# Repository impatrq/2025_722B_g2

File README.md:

# AQUILES - Exoesqueleto de Asistencia Motora

<div align="center">
  
  <h3>Revolucionando la movilidad humana</h3>
  <p>Exoesqueleto de asistencia motora con inteligencia artificial</p>
  
  <!-- Íconos de redes sociales -->
<p align="center">
  &nbsp;&nbsp;&nbsp;&nbsp;
  &nbsp;&nbsp;&nbsp;&nbsp;
  &nbsp;&nbsp;&nbsp;&nbsp;
  
</p>
</div>

## 🌐 Accede a la Página Web

🔗 [Visita Aquiles Web](https://aquilesproject.com/)

## ✨ Revolucionando la Movilidad Humana

AQUILES es un exoesqueleto de asistencia motora diseñado para mejorar la movilidad de personas con debilidad muscular, fatiga crónica o dificultades motrices. Este sistema innovador reduce el esfuerzo físico del usuario, permitiendo una marcha más eficiente y menos agotadora.

## 🔧 Características Principales

- **Asistencia Inteligente**: AQUILES integra inteligencia artificial para adaptar su funcionamiento a las necesidades del usuario en tiempo real.
- **Sistema de Ajuste**: Un botón permite regular el nivel de asistencia, facilitando la rehabilitación progresiva y el fortalecimiento muscular.
- **Diseño Ergonómico y Ligero**: Fabricado con materiales resistentes y de bajo peso para garantizar comodidad y facilidad de uso.
- **Sensores Avanzados**: Incluye acelerómetros y encoders para monitorear el movimiento y optimizar la asistencia.
- **Monitor de Salud**: Registra calorías quemadas y mide el pulso mediante un sensor ubicado en la arteria femoral.
- **Aplicaciones en Rehabilitación**: Ideal para programas médicos donde los especialistas pueden ajustar la asistencia según la evolución del paciente.
- **Baterías Intercambiables**: Ofrece una autonomía de 45 minutos con baterías compactas y fáciles de reemplazar.

## 👨‍👩‍👦🛠️ Aplicaciones

- **Personas con movilidad reducida**: AQUILES reduce el esfuerzo necesario para caminar.
- **Personas con sobrepeso o alta estatura**: Ayuda a disminuir la carga en articulaciones y músculos.
- **Adultos mayores**: Facilita la marcha y reduce la fatiga muscular.
- **Rehabilitación física**: Ajuste progresivo para recuperar fuerza y movilidad.
- **Deporte y fitness**: Apoya la resistencia y optimiza el rendimiento físico.

## ⚡ Tecnología Utilizada

- **Hardware**:

  - Raspberry Pi 4
  - Sensores de aceleración y encoders
  - Motores brushless con controladores ESC
  - Baterías LiPo 3S 5000mAh 70C
  - Pulsadores y sistema de ajuste de asistencia

- **Software**:
  - Programación en C/C++ y Python
  - Algoritmos de Machine Learning para optimización de asistencia
  - Integración con microcontroladores RP2040
  - Flutter para la aplicación móvil
  - Firebase para la base de datos

## 💸 Costos Estimados

El desarrollo de AQUILES tiene un costo estimado de **378 USD**, incluyendo componentes electrónicos, motores y materiales de fabricación.

## 📢 Contribución

Si deseas colaborar con el desarrollo de AQUILES, puedes contribuir con:

- Mejoras en el código
- Optimización de hardware
- Documentación y pruebas
- Aportes económicos para investigación y desarrollo

## 🛠️ Instalación y Uso

1. Clona el repositorio:
   ```bash
   git clone https://github.com/tu-usuario/aquiles.git
   ```
2. Instala las dependencias necesarias.
3. Carga el firmware en la Raspberry Pi 4.
4. Conecta los motores y sensores.
5. Ajusta el nivel de asistencia y comienza a probar AQUILES.

## 📈 Futuro del Proyecto

- Implementación de algoritmos de IA más avanzados.
- Desarrollo de una aplicación móvil para el monitoreo en tiempo real.
- Optimización del consumo energético para aumentar la autonomía.
- Pruebas con usuarios reales para mejorar la experiencia de uso.

## Integrantes:

### Juan Montilla

- 📷 Instagram: [@montillajuanignacio](https://www.instagram.com/montillajuanignacio/)
- 📧 Mail: montillajuanignacio@gmail.com
- 🏆 LinkedIn:[Juan Montilla](https://www.linkedin.com/in/juan-ignacio-montilla-b98064358/)
- 🌐 Github: [@monti3](github.com/monti3)

### Santiago Alberto Zacarías

- 📷 Instagram: [@santizaca\_](https://www.instagram.com/santizaca_/)
- 📧 Mail: sanfran120771@gmail.com
- 🏆 LinkedIn: [Santiago Zacarias](https://www.linkedin.com/in/santiago-zacar%C3%ADas-3a3978319/)
- 🌐 Github: [ZaCoso](https://github.com/ZaCoso)

### Juan Cruz Isola

- 📷 Instagram: [@juanisola\_](https://www.instagram.com/juanisola_/)
- 📧 Mail: juancruz.isola2209@gmail.com
- 🏆 LinkedIn: [Juan Cruz Isola](https://www.linkedin.com/in/juan-cruz-isola-11309035a/)
- 🌐 Github: [juanisola\_](https://github.com/juanisola)

### Rodrigo Alexis Lin

- 📷 Instagram: [@alexisrodrigolin](https://www.instagram.com/alexisrodrigolin/)
- 📧 Mail: alexisrodrigolin@gmail.com
- 🏆 LinkedIn: [Rodrigo Alexis Lin](https://www.linkedin.com/in/rodrigo-lin-61210a35b/)
- 🌐 Github: [alexisrodrigolin](https://github.com/alexisrodrigolin)

### Mauricio Contardi Trillo

- 📷 Instagram: [@mauritrillo\_](https://www.instagram.com/mauritrillo_/)
- 📧 Mail: trillocontardimauricio@gmail.com
- 🏆 LinkedIn: [Mauricio Contardi Trillo](https://www.linkedin.com/in/mauricio-trillo-contardi-68bbba35a/)
- 🌐 Github: [Mauriciotrillo](https://github.com/MauricioTrillo)

### Misael Castillo

- 📷 Instagram: [@misaacas](https://www.instagram.com/misaacas/)
- 📧 Mail: misacastillo08@gmail.com
- 🏆 LinkedIn: [Castillo Misael](https://www.linkedin.com/in/misael-castillo-0a52a1314/)
- 🌐 Github: [misaacastillo](https://github.com/misaacastillo)

---

AQUILES es más que un proyecto tecnológico: es una solución que redefine la movilidad humana. ¡Sé parte de la revolución! 💪🛠️

## 📜 Licencia

Este proyecto está licenciado bajo la [MIT License](LICENSE).  
© 2025 Aquiles.corp.

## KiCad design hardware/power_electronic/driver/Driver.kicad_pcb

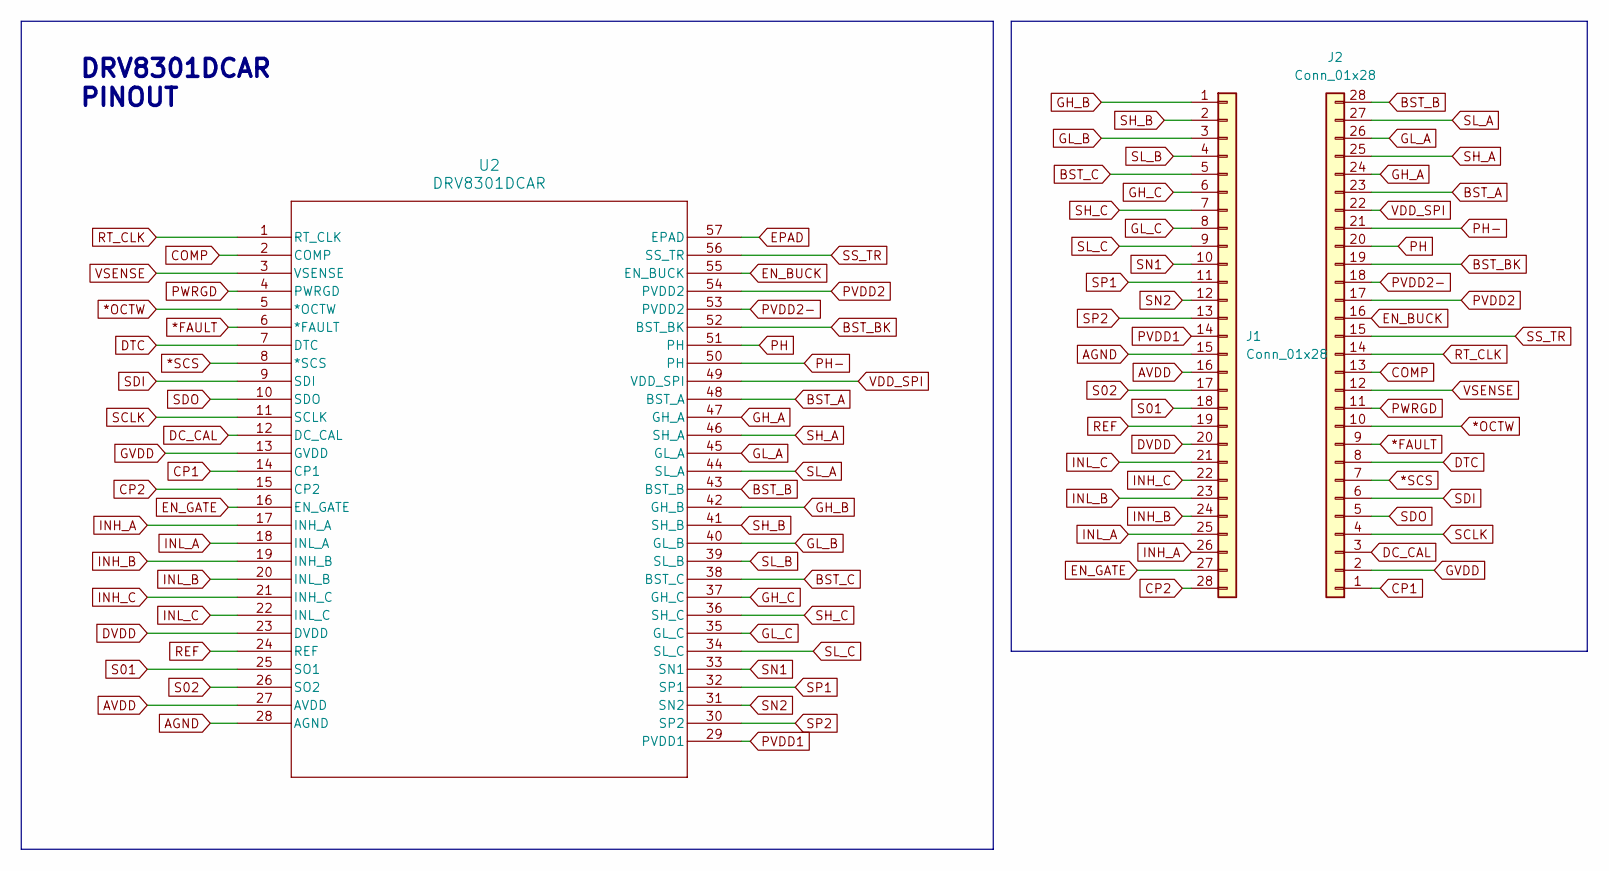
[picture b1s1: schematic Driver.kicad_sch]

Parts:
J1, J2: Conn_01x28; PinHeader_1x28_P2.54mm_Vertical
U2: DRV8301DCAR; DRV8301DCAR PADGND

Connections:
*FAULT: J2.9, U2.6 (*FAULT)
*OCTW: J2.10, U2.5 (*OCTW)
*SCS: J2.7, U2.8 (*SCS)
AGND: J1.15, U2.28 (AGND)
AVDD: J1.16, U2.27 (AVDD)
BST_A: J2.23, U2.48 (BST_A)
BST_B: J2.28, U2.43 (BST_B)
BST_BK: J2.19, U2.52 (BST_BK)
BST_C: J1.5, U2.38 (BST_C)
COMP: J2.13, U2.2 (COMP)
CP1: J2.1, U2.14 (CP1)
CP2: J1.28, U2.15 (CP2)
DC_CAL: J2.3, U2.12 (DC_CAL)
DTC: J2.8, U2.7 (DTC)
DVDD: J1.20, U2.23 (DVDD)
EN_BUCK: J2.16, U2.55 (EN_BUCK)
EN_GATE: J1.27, U2.16 (EN_GATE)
EPAD: U2.57 (EPAD)
GH_A: J2.24, U2.47 (GH_A)
GH_B: J1.1, U2.42 (GH_B)
GH_C: J1.6, U2.37 (GH_C)
GL_A: J2.26, U2.45 (GL_A)
GL_B: J1.3, U2.40 (GL_B)
GL_C: J1.8, U2.35 (GL_C)
GVDD: J2.2, U2.13 (GVDD)
INH_A: J1.26, U2.17 (INH_A)
INH_B: J1.24, U2.19 (INH_B)
INH_C: J1.22, U2.21 (INH_C)
INL_A: J1.25, U2.18 (INL_A)
INL_B: J1.23, U2.20 (INL_B)
INL_C: J1.21, U2.22 (INL_C)
PH: J2.20, U2.51 (PH)
PH-: J2.21, U2.50 (PH)
PVDD1: J1.14, U2.29 (PVDD1)
PVDD2: J2.17, U2.54 (PVDD2)
PVDD2-: J2.18, U2.53 (PVDD2)
PWRGD: J2.11, U2.4 (PWRGD)
REF: J1.19, U2.24 (REF)
RT_CLK: J2.14, U2.1 (RT_CLK)
S01: J1.18, U2.25 (SO1)
S02: J1.17, U2.26 (SO2)
SCLK: J2.4, U2.11 (SCLK)
SDI: J2.6, U2.9 (SDI)
SDO: J2.5, U2.10 (SDO)
SH_A: J2.25, U2.46 (SH_A)
SH_B: J1.2, U2.41 (SH_B)
SH_C: J1.7, U2.36 (SH_C)
SL_A: J2.27, U2.44 (SL_A)
SL_B: J1.4, U2.39 (SL_B)
SL_C: J1.9, U2.34 (SL_C)
SN1: J1.10, U2.33 (SN1)
SN2: J1.12, U2.31 (SN2)
SP1: J1.11, U2.32 (SP1)
SP2: J1.13, U2.30 (SP2)
SS_TR: J2.15, U2.56 (SS_TR)
VDD_SPI: J2.22, U2.49 (VDD_SPI)
VSENSE: J2.12, U2.3 (VSENSE)

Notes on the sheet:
DRV8301DCAR PINOUT

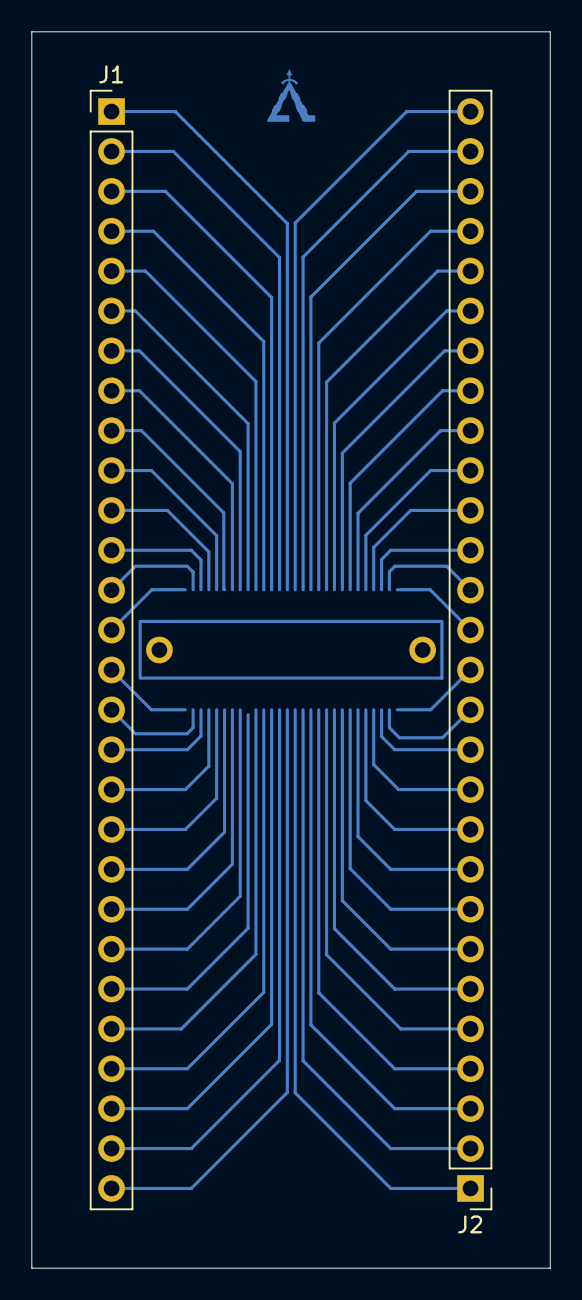
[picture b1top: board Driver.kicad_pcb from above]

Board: 2 copper layers, 33.0 x 78.7 mm, 3 parts (1 on the bottom side), 56 nets.

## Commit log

2025-04-09 Feat: copiado de mails
2025-04-09 Feat: Agregado de imagen
2025-04-09 Feat: Mouse Hover Function
2025-04-09 feat: agregar dominio web
2025-04-09 fix: direccion de imagen
2025-04-09 docs: actualizo texto sobre aquiles
2025-04-09 docs: actualizo texto nuestra mision
2025-04-09 style: elimino recuadro logo acerca de nosotros
2025-04-09 refactor: reordeno carpetas de assets
2025-04-09 feat: nueva imagen para logo acerca de nosotros
2025-04-09 style: cambio ui de login
2025-04-09 docs: actualizo imagen acerca de nosotros
2025-04-09 style: cmabio de estilo de la home con implementacion de tabbars
2025-04-09 feat: creo tab de status
2025-04-09 anado tab de rendimiento
2025-04-09 feat: anado tab de config
2025-04-09 refactor: reacomodo carpetas
2025-04-09 docs: agrega imagen nueva para prototipo v1.0.0
2025-04-09 docs: modifico direcciones de imagenes y cambio titulos en galeria
    agrego prototipo v1.0.0 y prueba del mismo
2025-04-09 refactor: elimino screens no usadas
2025-04-10 docs: agrego imagen nueva de rediseño de app
2025-04-10 feat: agrega enlaces de ig en la seccion footer.
2025-04-10 fix: modifica la imagen de la app y corrige enlace ig en la seccion footer
2025-04-10 style: modifica el recuadro de la app
    este commit modifica el recuadro de la app para que el movil se parezca a un iphone SE 3ra gen.
2025-04-10 Revert "style: modifica el recuadro de la app"
    This reverts commit 757a0f843cb051f1aa53acee0bc563448c5307ce.
2025-04-10 Reapply "style: modifica el recuadro de la app"
    This reverts commit 2ff444efee2d17f3c72c1c0935f9941b9f02e683.
2025-04-10 Revert "Reapply "style: modifica el recuadro de la app""
    This reverts commit 35cd3990031cbd8042046561c2b80350e4764c74.
2025-04-10 Reapply "Reapply "style: modifica el recuadro de la app""
    This reverts commit af200588cc74c726af259d7cd97acbf0a7c3e3ba.
2025-04-10 fix: cambia enlace de la web
2025-04-11 fix: arrregla el muestreo de imagen en web
2025-04-11 feat: agrega icono de web en paginas de navegacion
2025-05-23 feat: implement firebase
2025-05-25 feat: implemento firebase y riverpod
2025-05-26 style: corrijo logo
2025-05-26 feat: implemento login en consumerwidget
2025-05-26 fix: solucion stop en transicion de login a home
2025-05-26 refactor: elimino archivos sin usar
2025-05-26 fix: corrijo el user model
2025-05-26 feat: anado screen de perfil
2025-05-26 style: arreglo ui
2025-05-27 feat: userservice
2025-06-09 feat: implemento logout
2025-06-10 feat:implemento consultas a firebase
2025-06-12 refactor: move web files into Aquiles_Web directory
2025-06-12 refactor: renaming Aquiles_App directory
2025-06-12 fix: correct path for missing logo
2025-06-12 chore: add .gitignore
2025-06-12 chore: add -backups to .gitignore
2025-06-16 feat: creo tab de unconneted y bleservice
2025-06-16 feat: implemento boton para interactuar con BLEservice
2025-06-16 refactor: implemento providers para ble y status ble
2025-06-16 feat: se le envian commandos al dispositivo y .md de los commandos
2025-06-16 refactor: implemento formato de comandos en settings
2025-06-16 feat: incluyo capacidades de recibir desde la app
2025-06-16 feat: anado archivo test ble esp32
2025-06-18 Pagina Web V2
2025-06-18 feat: make adapter for DVR8301
2025-06-18 Feat: Lightbox Function
2025-06-18 Fix: logo UBP
2025-06-18 Fix: Linea vertical del "funcionamiento de Aquiles"
2025-06-20 Fix: header junto section en Aquiles A1
2025-06-20 Fix: imagen UBP
2025-06-20 Fix: Movable Y line Textbox
2025-06-20 Fix: Logo Centered
2025-06-22 feat: make Sensors testing .ino
2025-06-23 Feat: Front and back with dots to select description
2025-06-23 Fix: Coming soon alone with VOID.png
2025-06-23 Fix: Text Align
2025-06-23 Feat: Removal and addition of dots
2025-06-25 Fix: movable textbox
2025-06-25 Fix: New version of App
2025-06-26 fix: mpu not reading bug
2025-06-28 Feat: Sponsors Descriptivos
2025-06-28 Fix: Linkedin del proyecto
2025-06-28 Fix: Restyle de A1
2025-06-30 Fix: Sponsor card bullet points and description
2025-06-30 refactor: cambiar nombre de directore
2025-06-30 Remove .DS_Store files and update .gitignore
2025-07-02 Fix: style fixes
2025-07-02 feat: step_detection
2025-07-02 Fix: Especificaciones Técnicas Completas
2025-07-02 Feat: Imagenes del Progreso de Aquiles
2025-07-03 fix: library correction
2025-07-03 Feat: Redesign de Mobile View
2025-07-03 Fix: Nombres de imagenes
2025-07-03 fix: drv footprint correction
2025-07-03 chore: rename folders
2025-07-08 feat: agrega bibliotecas raspberry - simplefoc
2025-07-08 feat: agrega codigo preuba pwm para rp2040
    Codigo de preuba 2040Zero pwm
2025-07-08 feat: agrega codigo simplefoc drv8301dcar
2025-07-08 feat: SimpleFoc for Esp32 testing
2025-07-14 README.md
2025-07-14 chore: borro aux.txt
    Se borra este archivo porque causa conflictos en windows a la hora de clonar el repo
2025-07-14 docs: agrego carpeta de campo
2025-07-15 feat: power board
2025-07-15 feat: logos
